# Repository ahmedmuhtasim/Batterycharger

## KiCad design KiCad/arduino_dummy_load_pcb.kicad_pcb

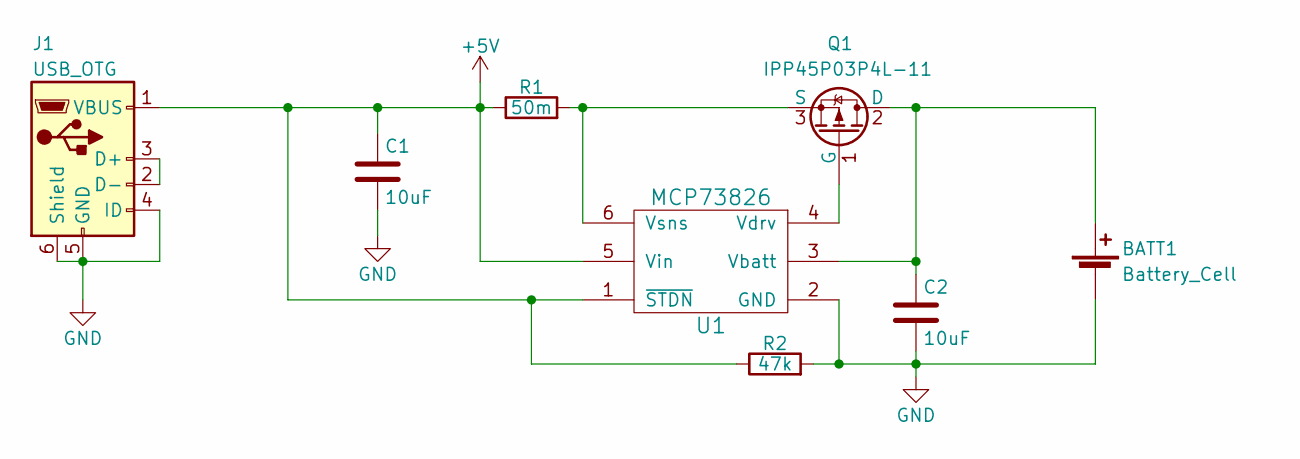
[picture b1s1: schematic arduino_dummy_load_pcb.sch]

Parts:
BATT1: Battery_Cell; 18650
C1, C2: 10uF; C_0805_HandSoldering
J1: USB_OTG; USB_Micro-B_Wuerth-629105150521_CircularHoles
Q1: IPP45P03P4L-11; TO-220-3_Vertical
R1: 50m; R_2512_HandSoldering
R2: 47k; R_0805_HandSoldering
U1: MCP73826; SOT-23-6_Handsoldering

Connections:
+5V: C1.1, J1.1 (VBUS), R1.1, R2.1, U1.1 (~STDN), U1.5 (Vin)
GND: BATT1.2 (-), C1.2, C2.2, J1.4 (ID), J1.5 (GND), J1.6 (Shield), R2.2, U1.2 (GND)
unnamed: BATT1.1 (+), C2.1, Q1.2 (D), U1.3 (Vbatt)
unnamed: J1.2 (D-), J1.3 (D+)
unnamed: Q1.1 (G), U1.4 (Vdrv)
unnamed: Q1.3 (S), R1.2, U1.6 (Vsns)

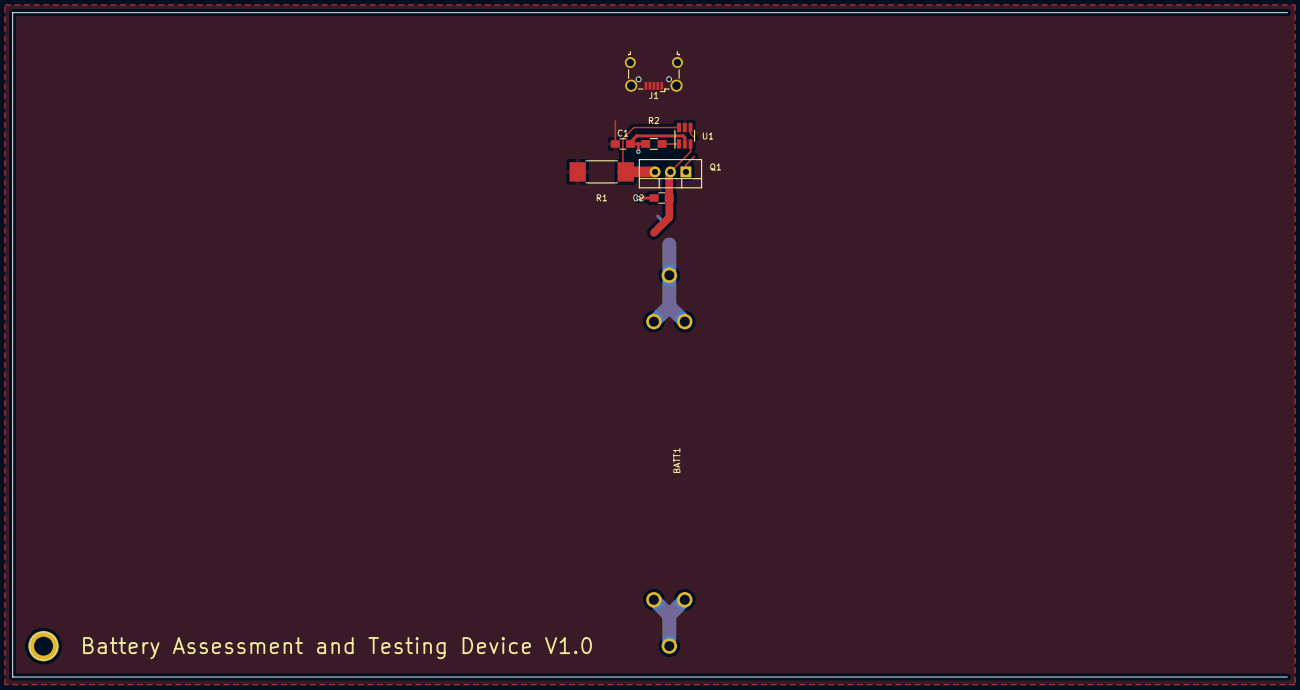
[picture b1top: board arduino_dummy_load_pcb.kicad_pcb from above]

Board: 2 copper layers, 209.6 x 109.2 mm, 8 parts (0 on the bottom side), 6 nets.

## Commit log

2018-01-24 initial commit (just took the Batterytester repo and deleted all but a single battery charger circuit)
